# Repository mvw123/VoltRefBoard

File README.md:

Voltage Reference Board
=========================

Reference board for voltage calibration. 
Design files are in Eagle v 6.5.0 (free version).
The design is 5cm x 5cm to allow low cost manufacture. 

CAD B - Work in progress
========================

Cost reduced board
PCB setup to use the sick of beige acrylic case.

CAD A - [PCB ordered]
=====================

Board not used, 
PCB fabrication ordered from OSH park. 
Need to setup parts for ordering. 
2.5v and 5.0v voltage reference source from a 9v battery or from an external power source.
The use of >10V is slightly more accurate when using these precision reference ICs. 

MVW
www.guvvy.co.uk

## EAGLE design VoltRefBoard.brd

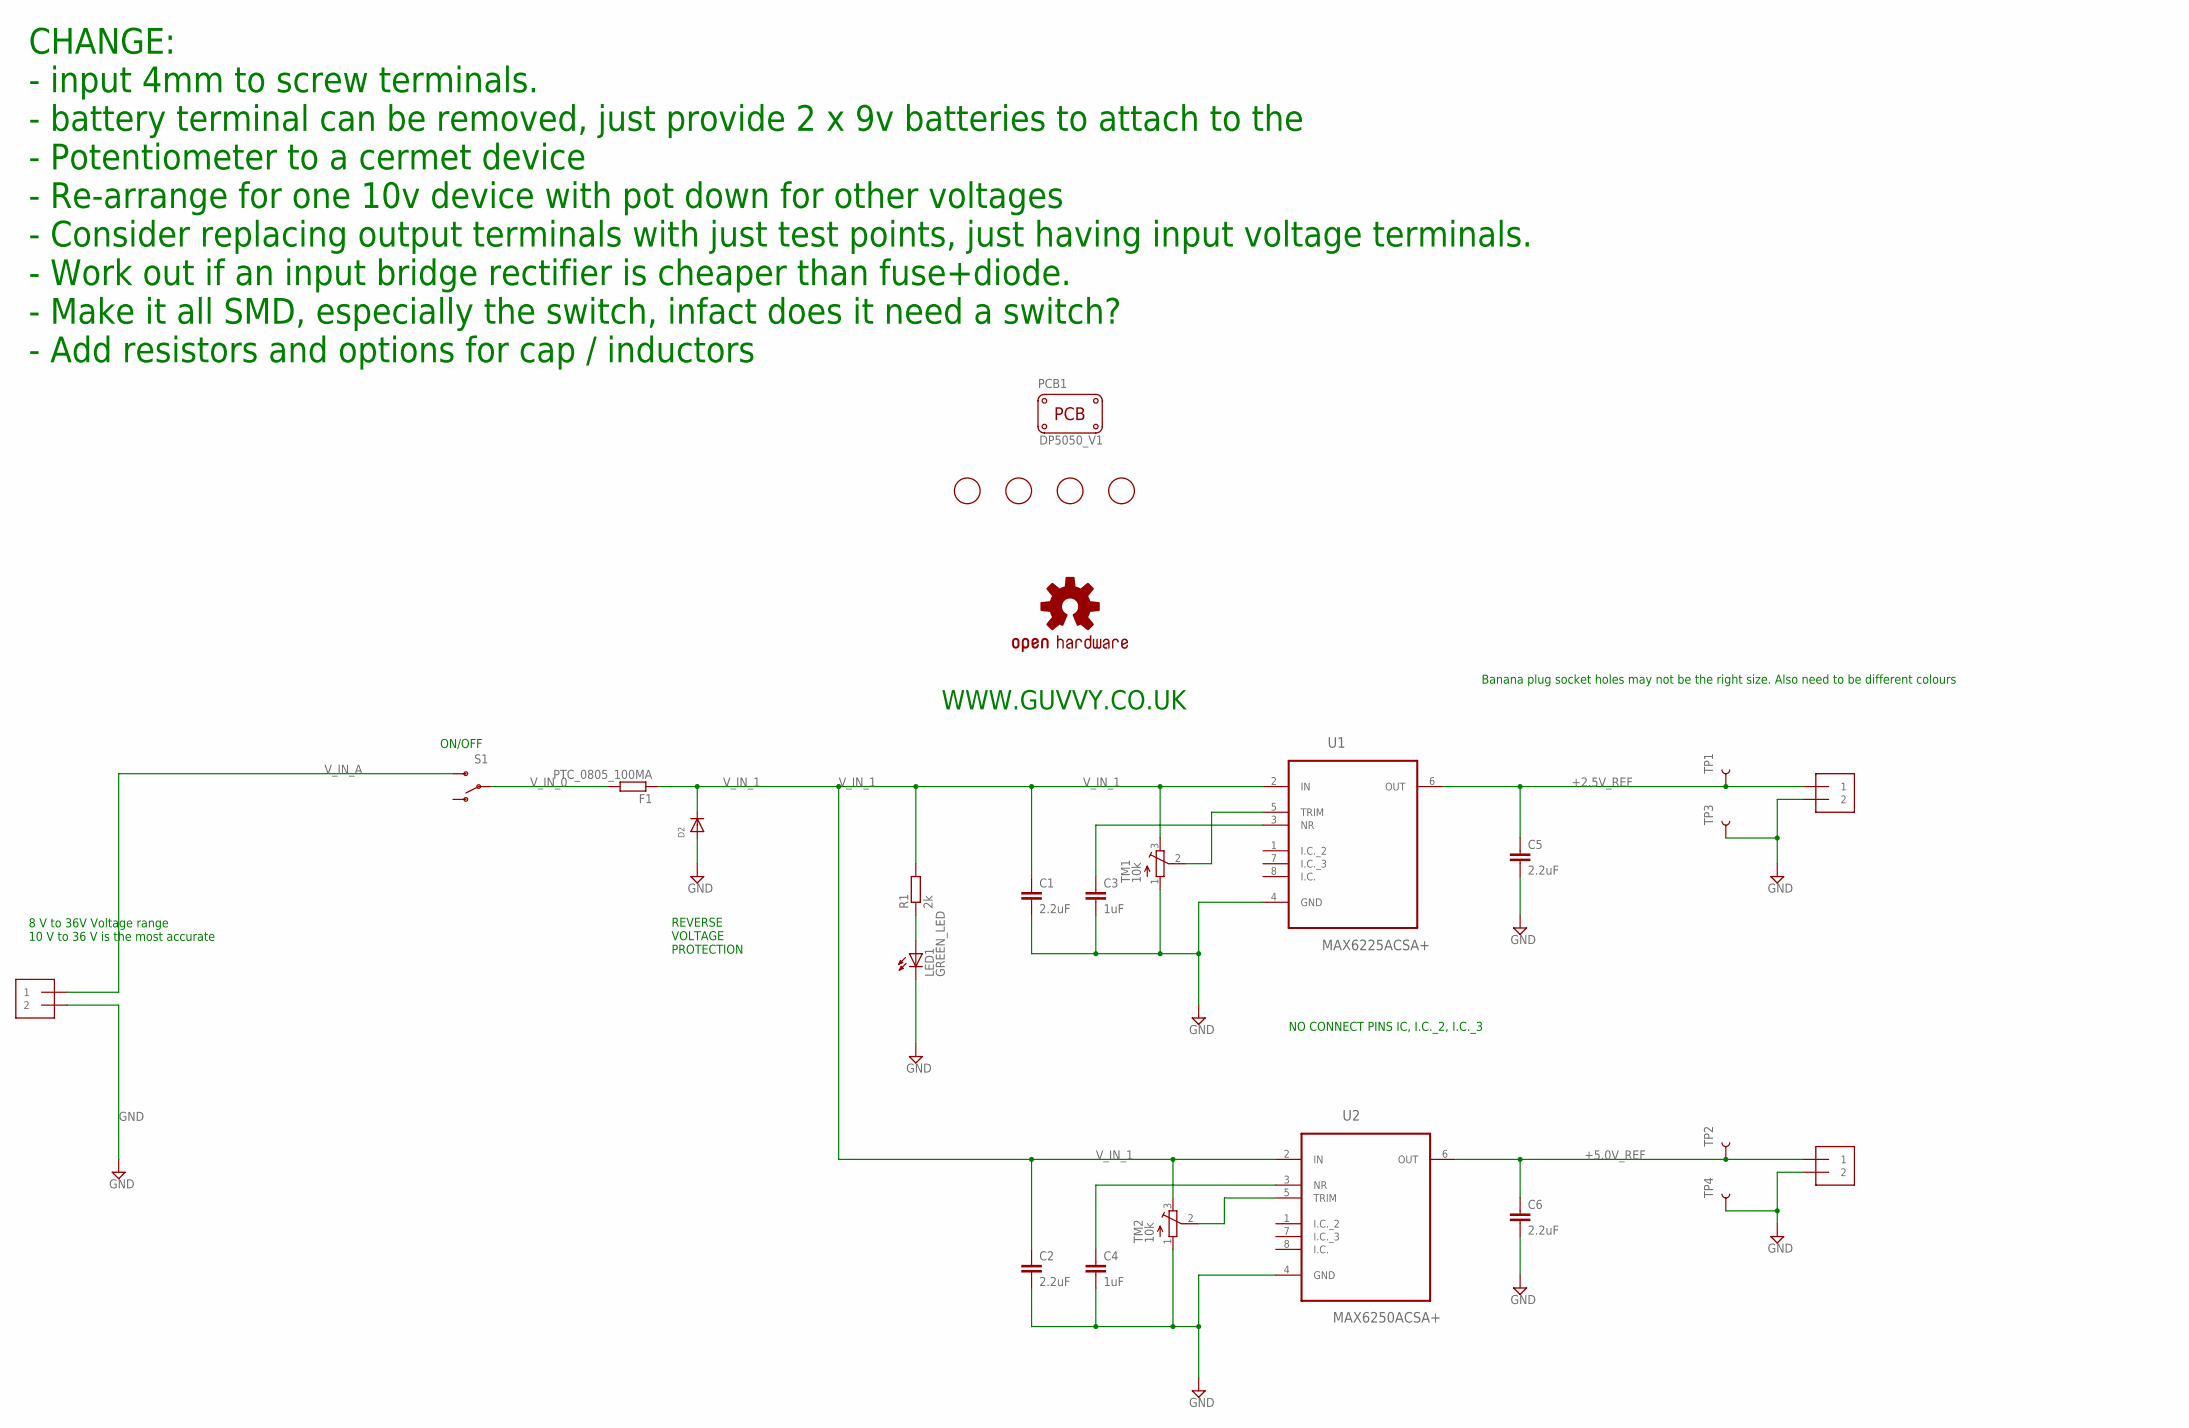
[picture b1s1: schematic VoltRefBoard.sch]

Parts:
C1, C2, C5, C6: 2.2uF; C0805
C3, C4: 1uF; C0805
D2: DIODESOD-323F; SOD-323F; MPN PMEG3010EJ,115
F1: PTC_0805_100MA; R0805; MPN MINISMDC110F/24-2
J1, J2, J6: 1X2-3.5MM
LED1: GREEN_LED; P-LCC-2; MPN LGT67K-H2K1-24-Z
LOGO1: OSHW-LOGOL; OSHW-LOGO-L
PCB1: PCB_DP_SQUARE-5X5; DP5050_V1
R1: 2k; R0805
S1: SWITCH-SPDT-SMD-A; SWITCH-SPST-SMD-A
TM1, TM2: 10k; TC33X; MPN TS53YJ103MR10
TP1, TP2, TP3, TP4: TP_1MM_TH"; TP_1MM_TH; MPN TEST-3
U1: MAX6225ACSA+; SOIC127P600X175-8N; MPN MAX6225ACSA+.
U2: MAX6250ACSA+; SOIC127P600X175-8N; MPN MAX6250ACSA+.
U$1, U$2, U$3, U$4: FIDUCIAL; FIDUCIAL_1MM

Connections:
+2.5V_REF: C5.1, J1.1, TP1.P$1, U1.6 (OUT)
+5.0V_REF: C6.1, J2.1, TP2.P$1, U2.6 (OUT)
GND: C1.2, C2.2, C3.2, C4.2, C5.2, C6.2, D2.A, J1.2, J2.2, J6.2, LED1.C, TM1.1 (A), TM2.1 (A), TP3.P$1, TP4.P$1, U1.4 (GND), U2.4 (GND)
unnamed: TM2.2 (S), U2.5 (TRIM)
unnamed: TM1.2 (S), U1.5 (TRIM)
unnamed: C4.1, U2.3 (NR)
unnamed: C3.1, U1.3 (NR)
unnamed: LED1.A, R1.1
V_IN_0: F1.2, S1.2
V_IN_1: C1.1, C2.1, D2.C, F1.1, R1.2, TM1.3 (E), TM2.3 (E), U1.2 (IN), U2.2 (IN)
V_IN_A: J6.1, S1.3 (S)

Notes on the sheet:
8 V to 36V Voltage range 10 V to 36 V is the most accurate
NO CONNECT PINS IC, I.C._2, I.C._3
REVERSE VOLTAGE PROTECTION
ON/OFF
WWW.GUVVY.CO.UK
Banana plug socket holes may not be the right size. Also need to be different colours
CHANGE: - input 4mm to screw terminals. - battery terminal can be removed, just provide 2 x 9v batteries to attach to the - Potentiometer to a cermet device - Re-arrange for one 10v device with pot down for other voltages - Consider replacing output terminals with just test points, just having inpu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

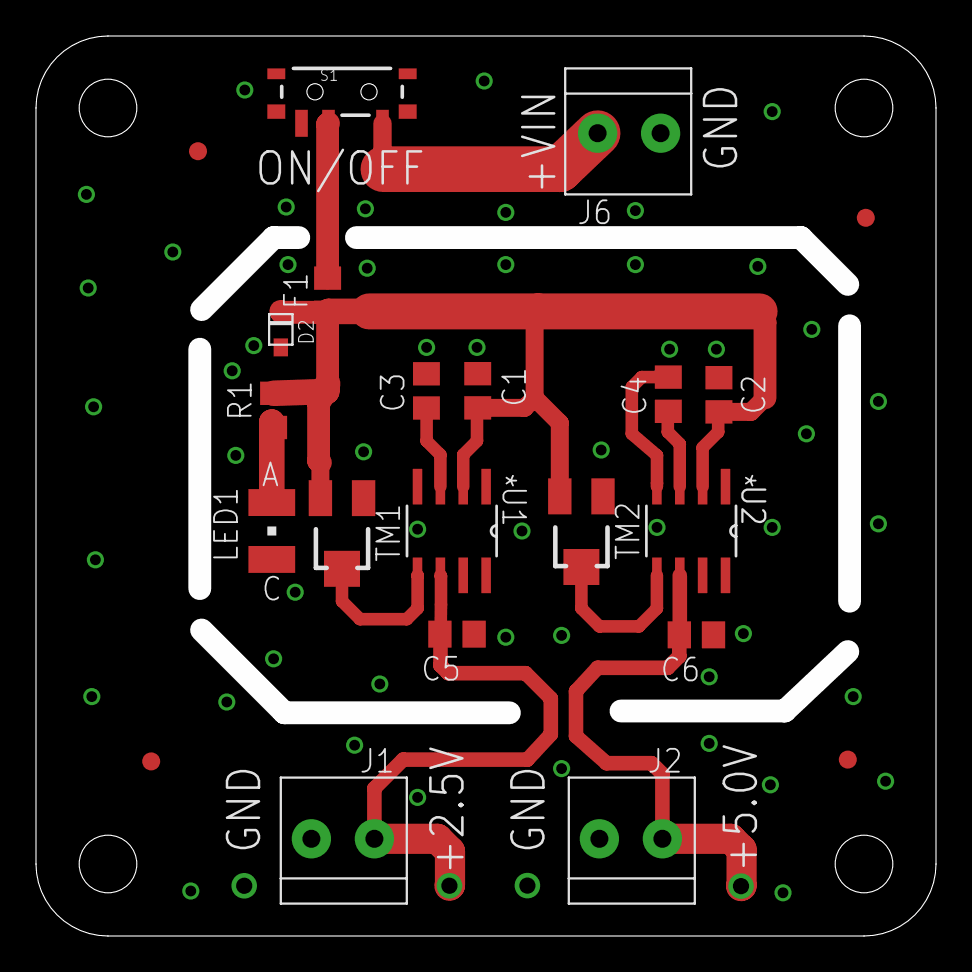
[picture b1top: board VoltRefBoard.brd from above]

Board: 2 copper layers, 48.7 x 48.7 mm, 28 parts (1 on the bottom side), 11 nets.

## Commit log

2014-12-27 CAD A PCB released for manufacture
    CAD A PCB released for manufacture
    Requires updates to the part numbers for purchasing
2014-12-27 Updated file names
    Updated file names and slightly amended the readme file
2014-12-27 minor typographical changes
2014-12-27 minor updates specifying eagle version
    minor updates specifying eagle version
2014-12-27 Minor change to project file
    Minor change to project file
2014-12-27 Changed title
    Changed title
2015-02-15 Latest commits
2016-01-16 Added the 5x5 pcbs from sick of beige
    Added the 5x5 pcbs from sick of beige and added cost down notes to the
    schematic to make it cheap to manufacture
2016-01-26 adding latest updates
    adding latest updates
2017-09-25 ds store updates
2018-01-19 minor updates

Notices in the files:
parts and their libraries:
SparkFun-Aesthetics: Licensing: Creative Commons ShareAlike 4.0 International - https://creativecommons.org/licenses/by-sa/4.0
